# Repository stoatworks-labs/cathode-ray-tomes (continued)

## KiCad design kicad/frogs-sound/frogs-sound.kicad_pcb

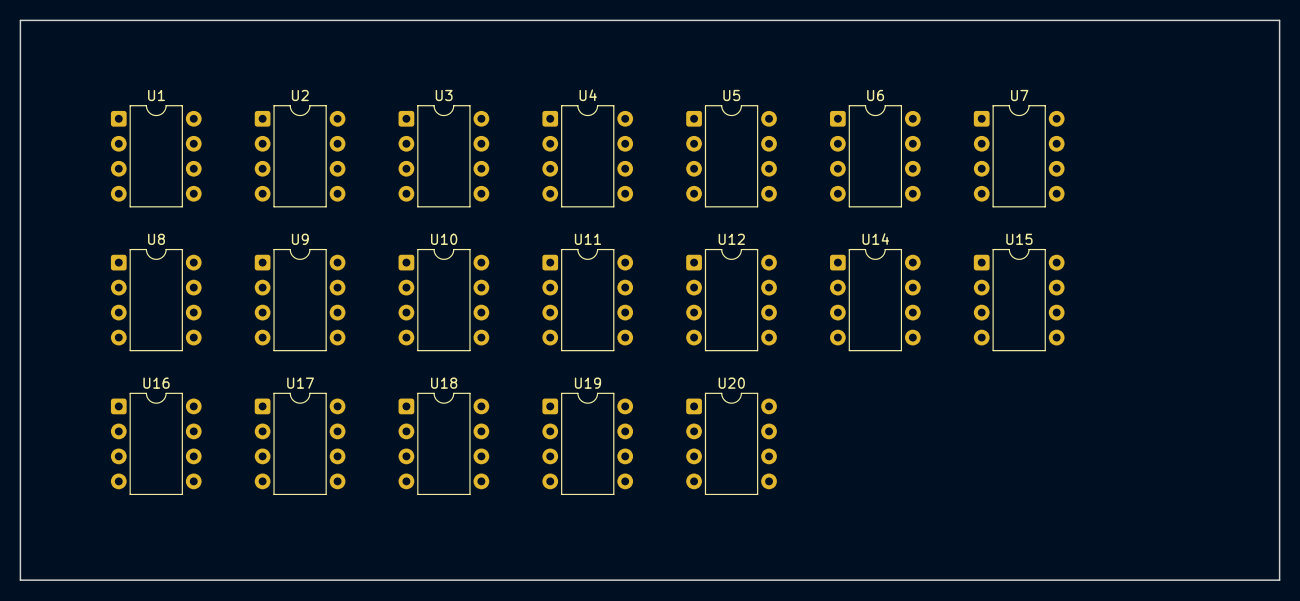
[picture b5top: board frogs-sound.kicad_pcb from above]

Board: 2 copper layers, 128.0 x 56.9 mm, 19 parts (0 on the bottom side), 16 nets, no tracks yet.

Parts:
U1: MM5837; DIP-8_W7.62mm
U2, U3, U4, U5, U6, U7, U9, U12, U15, U19: NE555; DIP-8_W7.62mm
U8, U10, U11, U14, U16, U17, U18, U20: LM741; DIP-8_W7.62mm

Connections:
+12V: U1.4, U2.4, U2.8, U3.4, U3.8, U4.4, U4.8, U5.4, U5.8, U6.4, U6.8, U7.8, U8.7, U9.8, U10.7, U11.7, U12.8, U14.7, U15.4, U15.8, U16.7, U17.7, U18.7, U19.4, U19.8, U20.7
-12V: U1.2, U8.4, U10.4, U11.4, U14.4, U16.4, U17.4, U18.4, U20.4
GND: U1.1, U2.1, U3.1, U4.1, U5.1, U6.1, U7.1, U8.3, U9.1, U10.3, U11.3, U12.1, U15.1, U16.3, U18.3, U19.1
unnamed: U2.6, U2.7
unnamed: U3.6, U3.7
unnamed: U4.6, U4.7
unnamed: U5.6, U5.7
unnamed: U6.6, U6.7
unnamed: U7.6, U7.7
unnamed: U12.2, U12.6
unnamed: U9.2, U9.6
unnamed: U15.2, U15.6, U15.7
unnamed: U19.2, U19.6
unnamed: U17.2, U17.6
unnamed: U7.2, U7.4, U12.4
unnamed: U3.3, U9.4
